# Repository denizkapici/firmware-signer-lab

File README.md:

# firmware-signer-lab

A button-approved release signer: a custom STM32F407 board, bare-metal
firmware that signs a release only after a physical button press, and a
host client that turns that signature into a single-use deployment
approval. Developed and tested entirely in simulation (Renode) and CI.

> **Status: lab project (v0.5).** The device generates its own Ed25519 key
> on first boot from the hardware RNG and only ever reveals the public
> key. Every signature carries a monotonic counter stored in flash. A
> secure bootloader starts only firmware signed with the release key. The key lives in ordinary MCU flash, so protect a real board with
> read-out protection; see [key management](docs/key-management.md), the
> [threat model](docs/threat-model.md) and the [roadmap](docs/roadmap.md).

## How it works

```mermaid
sequenceDiagram
    participant CI as CI / release job
    participant Host as signer-lab (host)
    participant Dev as Signer device (STM32F407)
    participant User as Human

    Note over Host,Dev: once: signer-lab enroll (PUBKEY) stores the device public key
    CI->>Host: approve firmware.bin --target staging
    Host->>Host: SHA-256, random 128-bit ID, expiry<br/>register operation in SQLite
    Host->>Dev: REQUEST3 id digest target expiry
    Dev-->>Host: PENDING3 ... (LED on)
    User->>Dev: presses button (fresh press, debounced)
    Dev->>Dev: counter = counter + 1 (stored in flash)<br/>Ed25519 sign "SIGNER-LAB-V3 id digest target expiry counter"
    Dev-->>Host: APPROVED3 ... counter signature
    Host->>Host: verify signature, re-hash file, counter newer?<br/>consume operation (once)
    Host-->>CI: ACCEPTED3 + receipt.json
```

The signature binds the file digest, the deployment target, an expiry
time and the device counter. The host accepts each approval exactly once,
also across restarts and concurrent processes, and never accepts an
approval older than the newest one it has seen from that device. A
receipt can be verified offline later.

## What is in the repository

| Part | Contents |
| --- | --- |
| [`hardware/`](hardware/) | KiCad 10 project: STM32F407VGT6 (LQFP-100), AP2112K-3.3 regulator, SWD, UART header, reset and approve buttons, status LED. 2-layer, 60 × 50 mm, ERC/DRC clean. |
| [`firmware/`](firmware/) | C11 and Thumb-2 assembly, no HAL or libc. Secure bootloader ([`firmware/boot/`](firmware/boot/)) that verifies the signed application image. Application: startup and full vector table, interrupt-driven UART with ring buffer, approval state machine, hardware RNG and flash drivers, on-device key generation and key store, wear-levelled monotonic counter in flash, fault reporting, watchdog, Ed25519 via vendored [Monocypher](https://monocypher.org) 4.0.3. |
| [`simulation/`](simulation/) | Renode platform matching the board's pins (UART4, PA0 button, PD12 LED). |
| [`host/signer_lab/`](host/signer_lab/) | Python client: V3 protocol, PTY/serial transport, receipts, SQLite single-use store with per-device counter tracking, CLI. |
| [`tests/`](tests/) | 96 Python unit tests (including the bootloader's C verifier built for the host); 42 Robot Framework tests in Renode (secure boot accept/reject paths, firmware behaviour, key generation and persistence, counter persistence, rotation and torn writes, end-to-end host ↔ firmware, Ed25519 on Cortex-M4). |
| [`docs/`](docs/) | [Protocol](docs/protocol.md), [secure boot](docs/secure-boot.md), [key management](docs/key-management.md), [threat model](docs/threat-model.md), [roadmap](docs/roadmap.md). |

## Quick start

Developed on Ubuntu 22.04 (aarch64); CI runs on Ubuntu 22.04 (x86_64).
Python 3.10 or newer.

```bash
sudo apt install gcc-arm-none-eabi binutils-arm-none-eabi python3-venv
python3 -m venv .venv && . .venv/bin/activate
pip install -r requirements/host.txt

./scripts/build-firmware.sh                         # bootloader + signed application (dev key)
python -m unittest discover -s tests -p 'test_*.py' # host tests, no device needed
```

Run the Renode tests ([Renode 1.17](https://github.com/renode/renode/releases/tag/v1.17.0)
with its `tests/requirements.txt` installed):

```bash
bash scripts/build-crypto-test.sh
SIGNER_HOST_PYTHON="$(command -v python)" /path/to/renode-test tests/*.robot
```

### Manual demo

Terminal 1 starts the simulated board with its UART on `/tmp/signer-uart`:

```bash
./scripts/run-renode.sh
```

Every new Renode session is a new, blank chip: the board generates a key
on boot. In terminal 2, enrol it once, then ask for approval:

```bash
./scripts/signer-lab enroll --port /tmp/signer-uart --key-out /tmp/device.hex

./scripts/signer-lab approve firmware/build/signer.bin \
  --port /tmp/signer-uart --database /tmp/approvals.sqlite3 \
  --target staging --receipt-out /tmp/approval.json \
  --public-key-file /tmp/device.hex
```

Press the button in the Renode monitor (terminal 1):

```
sysbus.gpioPortA.approveButton Press
sysbus.gpioPortA.approveButton Release
```

Then verify the receipt offline, and see that it cannot be used twice:

```bash
./scripts/signer-lab verify firmware/build/signer.bin \
  --receipt /tmp/approval.json --target staging --public-key-file /tmp/device.hex

./scripts/signer-lab accept firmware/build/signer.bin --receipt /tmp/approval.json \
  --database /tmp/approvals.sqlite3 --target staging --public-key-file /tmp/device.hex
# Error: Mismatched or already consumed approval.
```

## CI

Every push and pull request runs, on GitHub Actions:

- cppcheck on the firmware and ruff on the Python code;
- the Ed25519 known-answer test on the host;
- all Python tests;
- a bootloader and application build with `-Werror` and strict warnings,
  signed with a throwaway development key, with a size report;
- all Renode tests, booting through the secure bootloader, including
  tampered-image rejection, enrolment and a real approval over a PTY;
- offline verification of the receipt produced by that test, with the
  public key the simulated device generated.

Actions are pinned to commit SHAs and kept up to date by Dependabot.

## Limitations

- The key is in MCU flash; without read-out protection a debugger can
  read it (threat T1). Enrolment is trust on first use (T2a).
- No display: the button proves that someone was present, not that they
  saw what they approved (threat T5).
- Single use and the counter high-water mark are both kept in the host
  database; rolling it back re-opens approvals (threat T7). The device
  counter makes such a rollback visible but does not prevent it.
- Secure boot has no anti-rollback or A/B update path yet, and builds use
  a development firmware signing key (threats T10, T10a; roadmap 2b, 3).
- The PCB has not been manufactured. Renode runs its own STM32F4 model, so
  the tests validate the firmware, not the copper.

## License

MIT, see [LICENSE](LICENSE). Monocypher is dual-licensed BSD-2-Clause /
CC0, see [firmware/vendor/monocypher/LICENCE.md](firmware/vendor/monocypher/LICENCE.md).

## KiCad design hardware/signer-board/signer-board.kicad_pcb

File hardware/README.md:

# Hardware: signer-board (revision A)

KiCad 10 project in [`signer-board/`](signer-board/). Not manufactured yet.

| Item | Value |
| --- | --- |
| MCU | STM32F407VGT6, LQFP-100, internal 16 MHz HSI (no crystal) |
| Supply | 5 V on J3 → U2 AP2112K-3.3 LDO (EN tied to VIN) → 3.3 V; 1 µF on 5 V |
| Decoupling | nine 100 nF on 3.3 V, plus 1 µF ×3 and 4.7 µF bulk; VCAP1/VCAP2 2.2 µF each |
| Boot | R1 10 kΩ pull-down on BOOT0: boots from flash |
| Reset | NRST with 100 nF to GND (C15) and SW1 to GND; internal pull-up |
| Debug | J1, 5-pin SWD: 1 3V3, 2 SWDIO (PA13), 3 GND, 4 SWCLK (PA14), 5 NRST |
| UART | J2, 3-pin 3.3 V header: 1 PC10 (TX), 2 PC11 (RX), 3 GND |
| Approve button | SW2 from PA0 to 3.3 V, R3 10 kΩ pull-down (pressed = high) |
| Status LED | D1 on PD12 through R2 1 kΩ |
| PCB | 2 layers, 60 × 50 mm, ground zones on both layers |

## Pin map shared with firmware and simulation

| Function | Pin | Firmware | Renode (`simulation/signer.repl`) |
| --- | --- | --- | --- |
| UART TX / RX | PC10 / PC11 | `firmware/uart.c` (UART4, AF8) | `sysbus.uart4` |
| Approve button | PA0 | `firmware/gpio.c` | `gpioPortA.approveButton` |
| Status LED | PD12 | `firmware/gpio.c` | `gpioPortD.statusLed` |

## Exporting fabrication and review files

Run from this directory with KiCad 10's `kicad-cli` (on Windows it is in
`C:\Program Files\KiCad\10.0\bin\`):

```bash
mkdir -p exports/gerber
kicad-cli sch export pdf  -o exports/signer-board-schematic.pdf signer-board/signer-board.kicad_sch
kicad-cli sch export bom  -o exports/signer-board-bom.csv      signer-board/signer-board.kicad_sch
kicad-cli pcb export gerbers -o exports/gerber/                signer-board/signer-board.kicad_pcb
kicad-cli pcb export drill   -o exports/gerber/                signer-board/signer-board.kicad_pcb
kicad-cli pcb render --side top -o exports/signer-board-top.png signer-board/signer-board.kicad_pcb
```

Commit `exports/` so the board can be reviewed without opening KiCad.

## Known gaps (planned for revision B)

- No reverse-polarity or ESD protection on the 5 V input.
- No USB connection; the UART needs an external USB-UART adapter.
- No mounting holes or test points.
- No display, so the user cannot see what is being approved.

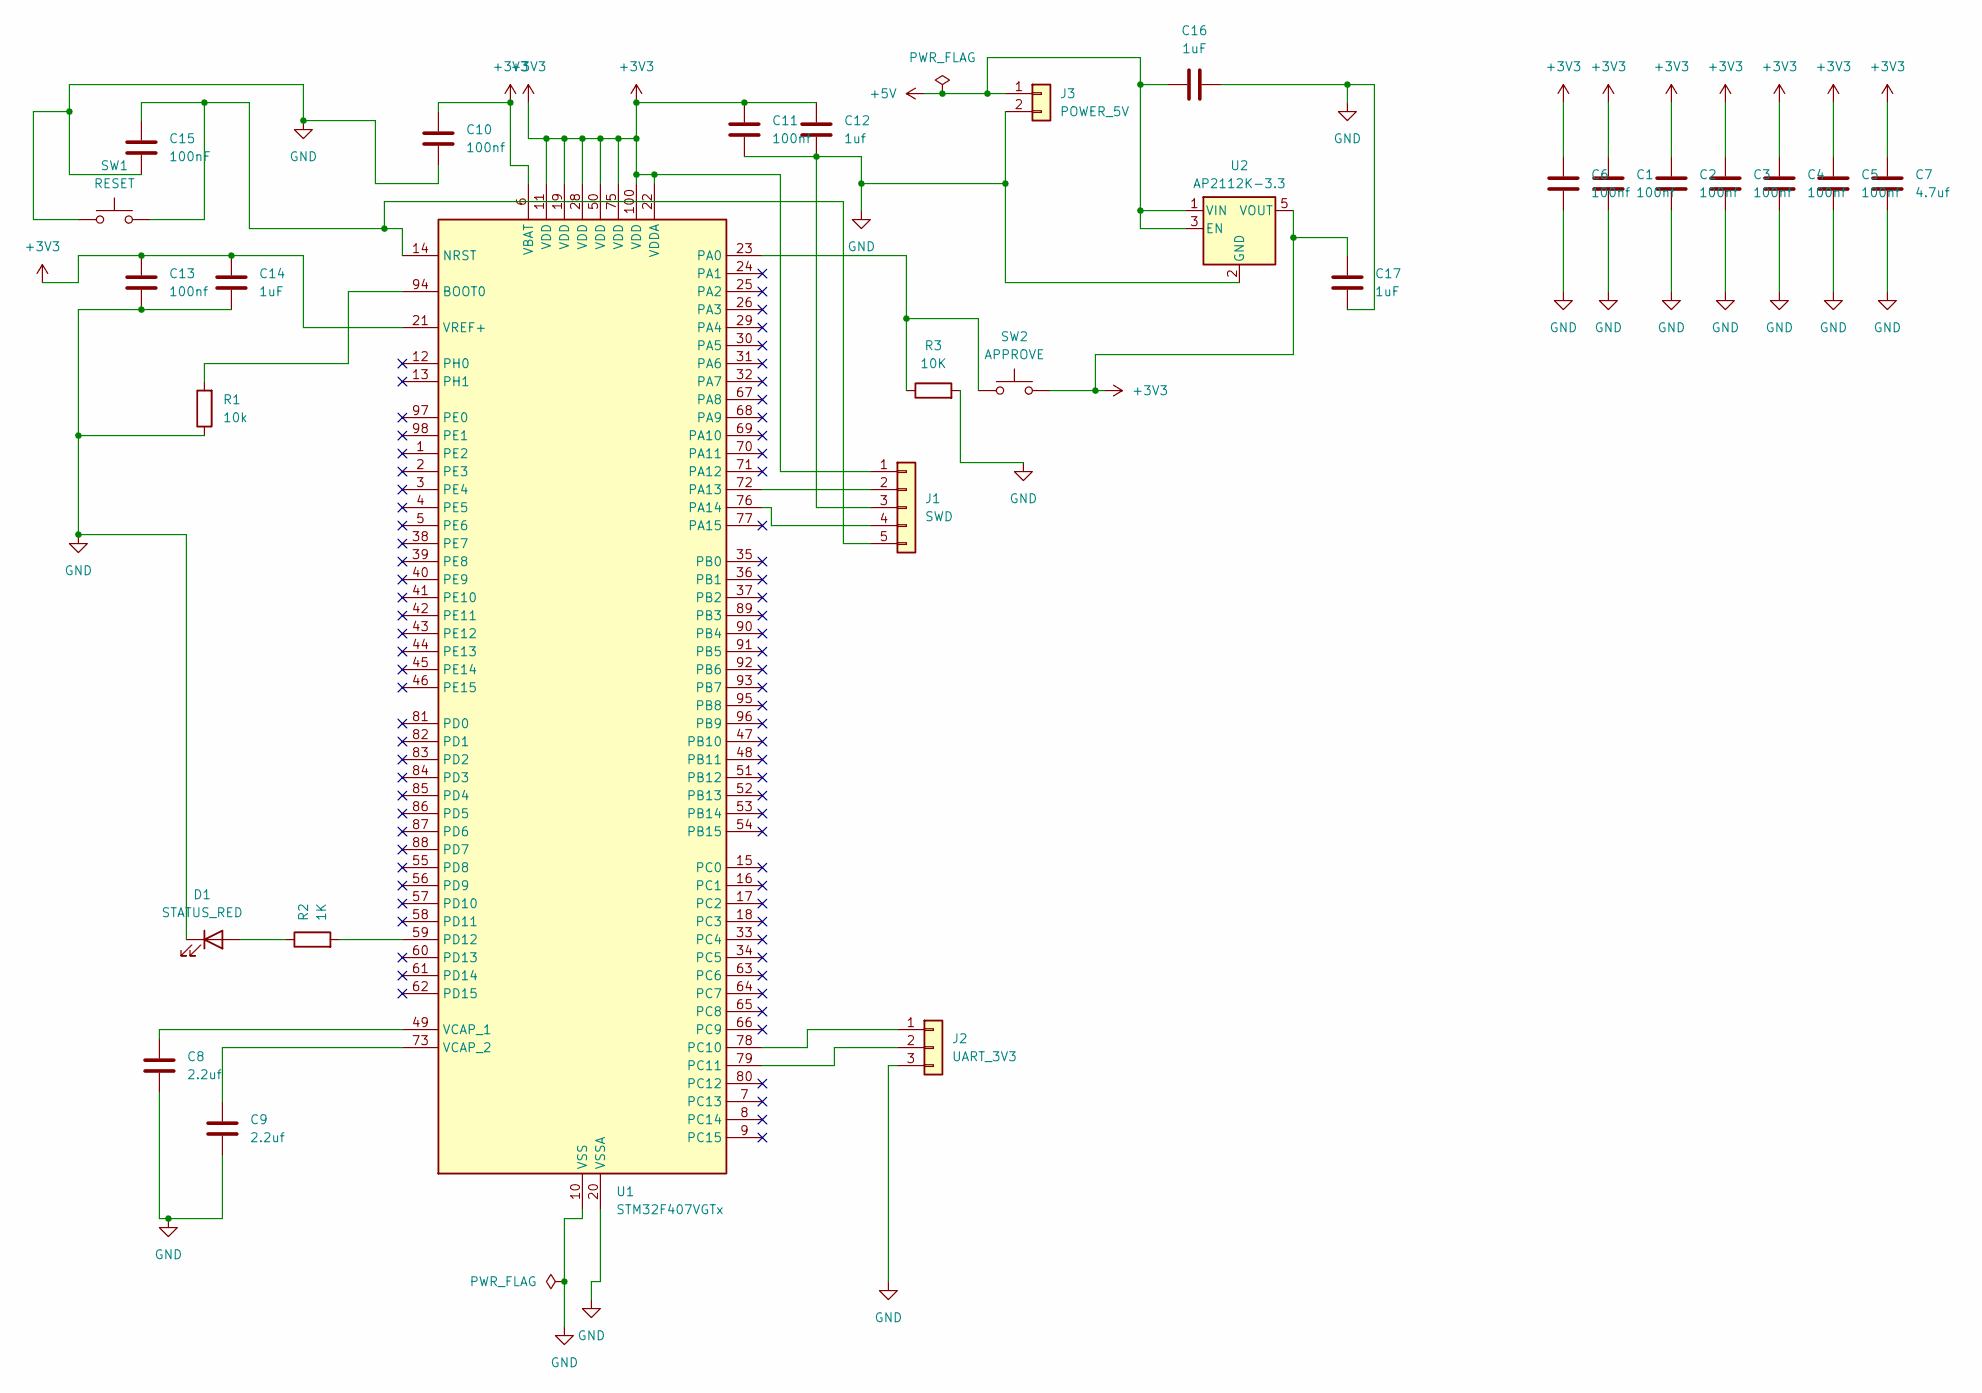
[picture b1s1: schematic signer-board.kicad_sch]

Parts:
C1, C2, C3, C4, C5, C6, C10, C11, C13: 100nf; C_0805_2012Metric
C7: 4.7uf; C_0805_2012Metric
C8, C9: 2.2uf; C_0805_2012Metric
C12: 1uf; C_0805_2012Metric
C14, C16, C17: 1uF; C_0805_2012Metric
C15: 100nF; C_0805_2012Metric
D1: STATUS_RED; LED_0805_2012Metric
J1: SWD; PinHeader_1x05_P2.54mm_Vertical
J2: UART_3V3; PinHeader_1x03_P2.54mm_Vertical
J3: POWER_5V; PinHeader_1x02_P2.54mm_Vertical
R1: 10k; R_0805_2012Metric
R2: 1K; R_0805_2012Metric
R3: 10K; R_0805_2012Metric
SW1: RESET; SW_PUSH_6mm
SW2: APPROVE; SW_PUSH_6mm
U1: STM32F407VGTx; LQFP-100_14x14mm_P0.5mm
U2: AP2112K-3.3; SOT-23-5

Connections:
+3V3: C1.1, C2.1, C3.1, C4.1, C5.1, C6.1, C7.1, C10.1, C11.1, C12.2, C13.1, C14.1, C17.2, J1.1, SW2.2, U1.6 (VBAT), U1.11 (VDD), U1.19 (VDD), U1.21 (VREF+), U1.22 (VDDA), U1.28 (VDD), U1.50 (VDD), U1.75 (VDD), U1.100 (VDD), U2.5 (VOUT)
+5V: C16.1, J3.1, U2.1 (VIN), U2.3 (EN)
GND: C1.2, C2.2, C3.2, C4.2, C5.2, C6.2, C7.2, C8.2, C9.2, C10.2, C11.2, C12.1, C13.2, C14.2, C15.2, C16.2, C17.1, D1.1 (K), J1.3, J2.3, J3.2, R1.1, R3.2, SW1.1, U1.10 (VSS), U1.20 (VSSA), U1.27 (VSS), U1.74 (VSS), U1.99 (VSS), U2.2 (GND)
unnamed: D1.2 (A), R2.1
unnamed: J1.2, U1.72 (PA13)
unnamed: J1.4, U1.76 (PA14)
unnamed: C15.1, J1.5, SW1.2, U1.14 (NRST)
unnamed: J2.1, U1.78 (PC10)
unnamed: J2.2, U1.79 (PC11)
unnamed: R1.2, U1.94 (BOOT0)
unnamed: R3.1, SW2.1, U1.23 (PA0)
unnamed: R2.2, U1.59 (PD12)
unnamed: C8.1, U1.49 (VCAP_1)
unnamed: C9.1, U1.73 (VCAP_2)

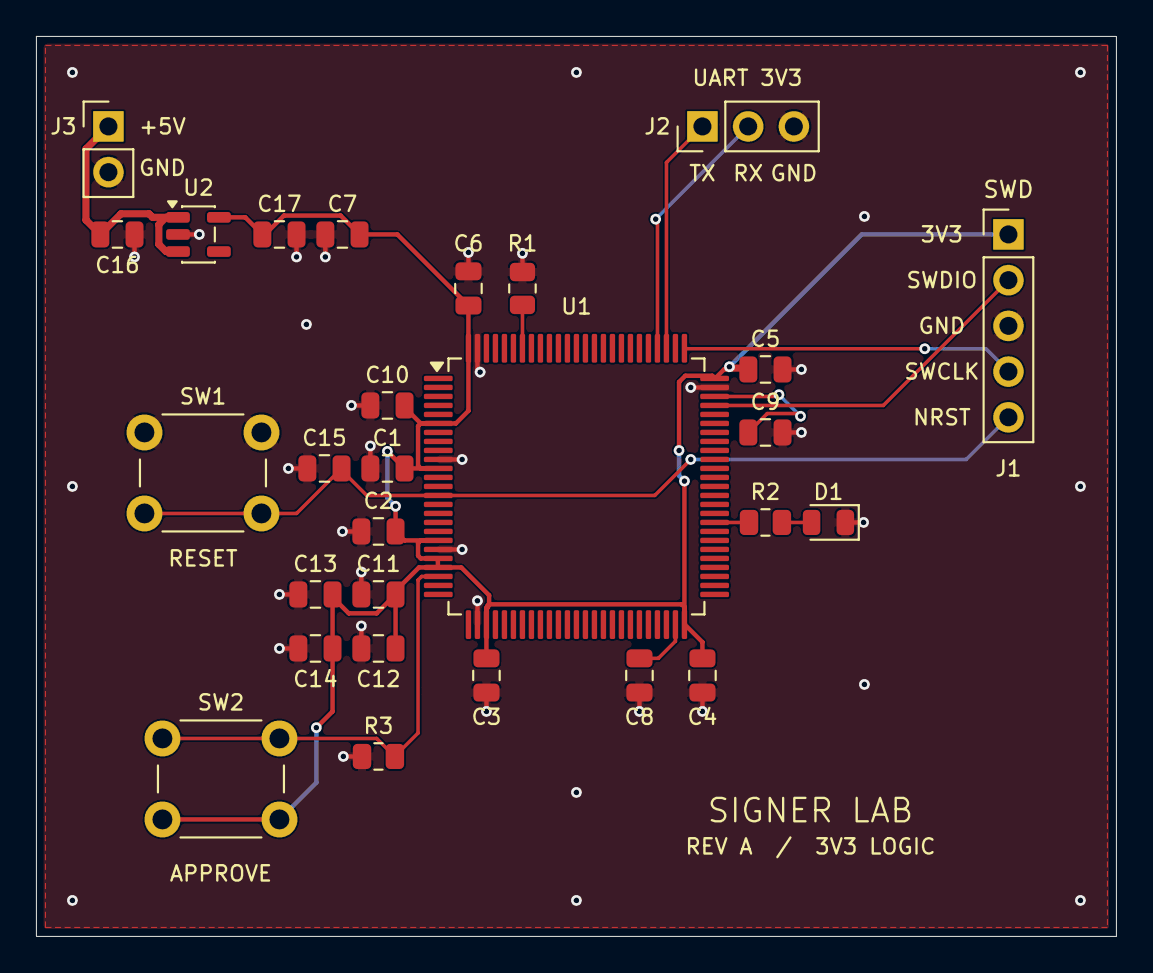
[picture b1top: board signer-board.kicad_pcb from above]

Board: 2 copper layers, 60.0 x 50.0 mm, 28 parts (0 on the bottom side), 14 nets.

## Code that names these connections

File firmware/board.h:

#ifndef SIGNER_BOARD_H
#define SIGNER_BOARD_H

/*
 * STM32F407 register map used by the signer firmware.
 * Only the registers the firmware touches are listed; addresses come from
 * RM0090 (STM32F405/407 reference manual).
 */

#include <stdint.h>

#define REG32(address) (*(volatile uint32_t *)(address))

/* Core clock after reset: 16 MHz HSI, no PLL. */
#define SIGNER_CORE_CLOCK_HZ 16000000u

/* RCC */
#define RCC_CR       REG32(0x40023800u)
#define RCC_PLLCFGR  REG32(0x40023804u)
#define RCC_CSR      REG32(0x40023874u)
#define RCC_AHB1ENR  REG32(0x40023830u)
#define RCC_AHB2ENR  REG32(0x40023834u)
#define RCC_APB1ENR  REG32(0x40023840u)

#define RCC_CR_PLLON  (1u << 24)
#define RCC_CR_PLLRDY (1u << 25)
#define RCC_AHB2ENR_RNGEN (1u << 6)

#define RCC_AHB1ENR_GPIOAEN (1u << 0)
#define RCC_AHB1ENR_GPIOCEN (1u << 2)
#define RCC_AHB1ENR_GPIODEN (1u << 3)
#define RCC_APB1ENR_UART4EN (1u << 19)

#define RCC_CSR_RMVF    (1u << 24)
#define RCC_CSR_IWDGRST (1u << 29)

/* GPIOA: approval button on PA0 */
#define GPIOA_MODER  REG32(0x40020000u)
#define GPIOA_PUPDR  REG32(0x4002000Cu)
#define GPIOA_IDR    REG32(0x40020010u)

/* GPIOC: UART4 TX/RX on PC10/PC11 */
#define GPIOC_MODER  REG32(0x40020800u)
#define GPIOC_AFRH   REG32(0x40020824u)

/* GPIOD: status LED on PD12 */
#define GPIOD_MODER  REG32(0x40020C00u)
#define GPIOD_OTYPER REG32(0x40020C04u)
#define GPIOD_PUPDR  REG32(0x40020C0Cu)
#define GPIOD_BSRR   REG32(0x40020C18u)

/* UART4 */
#define UART4_SR     REG32(0x40004C00u)
#define UART4_DR     REG32(0x40004C04u)
#define UART4_BRR    REG32(0x40004C08u)
#define UART4_CR1    REG32(0x40004C0Cu)

#define USART_SR_ORE   (1u << 3)
#define USART_SR_RXNE  (1u << 5)
#define USART_SR_TXE   (1u << 7)
#define USART_CR1_RE     (1u << 2)
#define USART_CR1_TE     (1u << 3)
#define USART_CR1_RXNEIE (1u << 5)
#define USART_CR1_UE     (1u << 13)

/* Random number generator */
#define RNG_CR       REG32(0x50060800u)
#define RNG_SR       REG32(0x50060804u)
#define RNG_DR       REG32(0x50060808u)

#define RNG_CR_RNGEN (1u << 2)
#define RNG_SR_DRDY  (1u << 0)
#define RNG_SR_CECS  (1u << 1)
#define RNG_SR_SECS  (1u << 2)
#define RNG_SR_CEIS  (1u << 5)
#define RNG_SR_SEIS  (1u << 6)

/* Embedded flash interface */
#define FLASH_KEYR   REG32(0x40023C04u)
#define FLASH_SR     REG32(0x40023C0Cu)
#define FLASH_CR     REG32(0x40023C10u)

#define FLASH_SR_EOP      (1u << 0)
#define FLASH_SR_ERRORS   (0xF0u)          /* WRPERR, PGAERR, PGPERR, PGSERR */
#define FLASH_SR_BSY      (1u << 16)
#define FLASH_CR_PG       (1u << 0)
#define FLASH_CR_SER      (1u << 1)
#define FLASH_CR_PSIZE_32 (2u << 8)
#define FLASH_CR_STRT     (1u << 16)
#define FLASH_CR_LOCK     (1u << 31)

/*
 * Flash layout (see docs/secure-boot.md):
 *   sectors 0-1  0x08000000  32 KB  bootloader (firmware/boot/boot.ld)
 *   sector  2    0x08008000  16 KB  approval counter log A
 *   sector  3    0x0800C000  16 KB  key store
 *   sector  4    0x08010000  64 KB  approval counter log B
 *   sector  5    0x08020000 128 KB  application slot A (firmware/app.ld)
 *   sector  6    0x08040000 128 KB  application slot B (reserved)
 */
#define KEYSTORE_SECTOR  3u
#define KEYSTORE_ADDRESS 0x0800C000u

#define COUNTER_A_SECTOR  2u
#define COUNTER_A_ADDRESS 0x08008000u
#define COUNTER_A_SIZE    0x4000u
#define COUNTER_B_SECTOR  4u
#define COUNTER_B_ADDRESS 0x08010000u
#define COUNTER_B_SIZE    0x10000u

/* Application slots (sectors 5 and 6, 128 KB each). Slot B is reserved
 * for A/B updates. */
#define SLOT_A_ADDRESS 0x08020000u
#define SLOT_A_SIZE    0x20000u
#define SLOT_B_ADDRESS 0x08040000u
#define SLOT_B_SIZE    0x20000u

/* Independent watchdog */
#define IWDG_KR      REG32(0x40003000u)
#define IWDG_PR      REG32(0x40003004u)
#define IWDG_RLR     REG32(0x40003008u)
#define IWDG_SR      REG32(0x4000300Cu)

/* SysTick */
#define SYST_CSR     REG32(0xE000E010u)
#define SYST_RVR     REG32(0xE000E014u)
#define SYST_CVR     REG32(0xE000E018u)

/* NVIC and fault status (System Control Block) */
#define NVIC_ISER(n) REG32(0xE000E100u + 4u * (n))
#define SCB_SHCSR    REG32(0xE000ED24u)
#define SCB_CFSR     REG32(0xE000ED28u)
#define SCB_HFSR     REG32(0xE000ED2Cu)
#define SCB_MMFAR    REG32(0xE000ED34u)
#define SCB_BFAR     REG32(0xE000ED38u)

#define UART4_IRQn 52u

/* Handlers referenced from the vector table in startup.s. */
void SysTick_Handler(void);
void UART4_IRQHandler(void);
void fault_report(const uint32_t *frame) __attribute__((noreturn));

#endif
